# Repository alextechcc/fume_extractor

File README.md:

# Fume Extractor
A 3d printable fume extractor with a 555 PWM fan controller made in KiCad

- Currently I use a more powerful fan without PWM control, and have used the PWM signal to dim a 10W led driver

# Sources
- [Solder Fume Extractor 120 mm by koensmelt](https://www.thingiverse.com/thing:1436781)
- [Customizable Fan Grill Cover by mightynozzle](https://www.thingiverse.com/thing:2802474)

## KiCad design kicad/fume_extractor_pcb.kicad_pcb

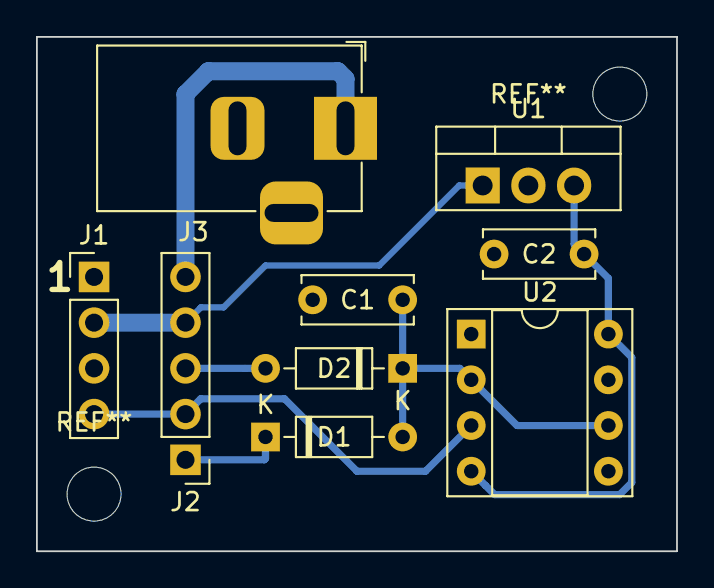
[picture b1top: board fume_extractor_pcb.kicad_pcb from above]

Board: 2 copper layers, 35.6 x 28.6 mm, 9 parts (0 on the bottom side), 8 nets.

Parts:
C1: 1nF; C_Disc_D6.0mm_W2.5mm_P5.00mm
C2: 0.1uF; C_Disc_D6.0mm_W2.5mm_P5.00mm
D1, D2: 1N4148; D_DO-35_SOD27_P7.62mm_Horizontal
J1: FAN_CONN; PinHeader_1x04_P2.54mm_Vertical
J2: CONTROLS_CONN; PinHeader_1x05_P2.54mm_Vertical
J3: Barrel_Jack_Switch; BarrelJack_Horizontal
U1: L7805; TO-220-3_Vertical
U2: NE555; DIP-8_W7.62mm_Socket

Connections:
+5V: C2.2, U1.3, U2.4, U2.8
+12V: J1.2, J2.4, U1.1
/JACK+: J2.5, J3.1
/LEVEL: C1.1, D1.2, D2.1, U2.2, U2.6
/POT_L: D2.2, J2.3
/POT_M: J1.4, J2.2, U2.3
/POT_R: D1.1, J2.1
GND: C1.2, C2.1, J1.1, J3.2, J3.3, U1.2, U2.1
